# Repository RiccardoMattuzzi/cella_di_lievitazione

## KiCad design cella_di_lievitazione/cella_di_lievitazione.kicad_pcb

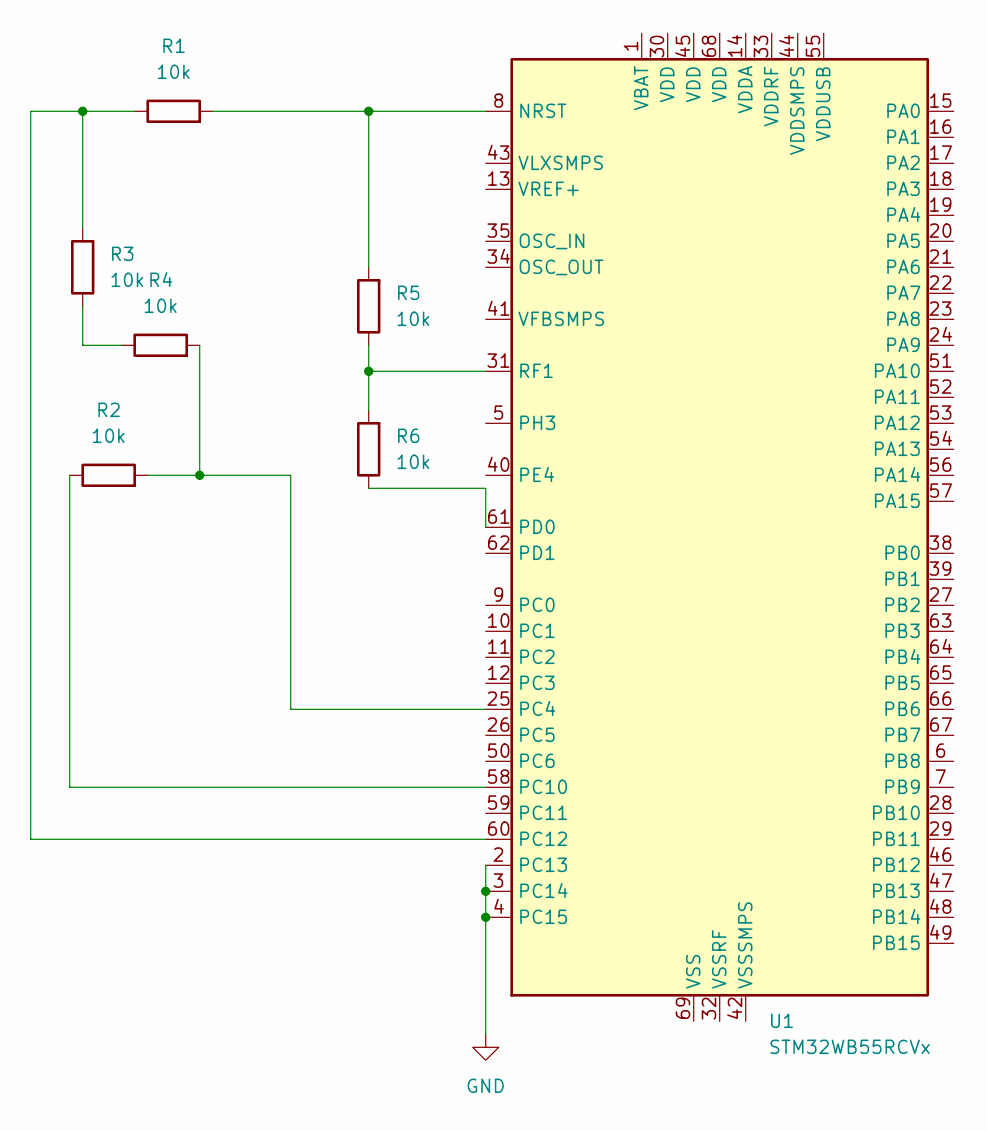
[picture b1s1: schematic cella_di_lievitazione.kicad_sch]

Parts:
R1, R2, R3, R4, R5, R6: 10k; R_0402_1005Metric
U1: STM32WB55RCVx; QFN-68-1EP_8x8mm_P0.4mm_EP6.4x6.4mm

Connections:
GND: U1.2 (PC13), U1.3 (PC14), U1.4 (PC15)
unnamed: R3.1, R4.1
unnamed: R1.2, R5.2, U1.8 (NRST)
unnamed: R2.2, R4.2, U1.25 (PC4)
unnamed: R2.1, U1.58 (PC10)
unnamed: R1.1, R3.2, U1.60 (PC12)
unnamed: R6.1, U1.61 (PD0)
unnamed: R5.1, R6.2, U1.31 (RF1)

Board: 2 copper layers, 7 parts (0 on the bottom side), 8 nets, no tracks yet.

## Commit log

2025-10-06 no message
2025-10-07 Messaggio di prova
2025-10-07 Modifiche minori
